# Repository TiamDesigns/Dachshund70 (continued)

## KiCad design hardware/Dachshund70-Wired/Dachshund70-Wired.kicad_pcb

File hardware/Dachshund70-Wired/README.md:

# Dachshund70 wired mainboard

Rev 1.4 (2026-11-24). A wired-only mainboard next to the tri-mode one (`hardware/Dachshund70/`, unchanged): no
radio, no battery, an RP2350B, an SK6812MINI-E under every key and hot-swap sockets on every key. KiCad 10, 2 layers,
same outline as mainboard rev 1.4 (x 19 to 326, y 39 to 160.1, the MCU column on the right), every part on the back,
so it drops into the same plate, case and flex.

Status: schematic ERC 0; board DRC clean (0 violations, 0 unconnected, schematic parity clean, kicad-cli 10.0.3).
Not ordered, not tested. No firmware yet: the RP2350 port is in `SCHEDULED_TASKS.md`.

Rev 1.0 had an RP2040 and a small SPI TFT; rev 1.1 swaps in the RP2350B so the screen can be a 2.41" AMOLED
(450 × 600, RM690B0 driver) on quad SPI, which the RP2040 couldn't drive at a useful frame rate. Rev 1.2 adds the
touch version of that screen: J4 grows to 16 pins for its touch controller's I2C, interrupt and reset. Rev 1.3
switches the screen to e-paper with capacitive touch, since the screen is mostly for changing settings; rev 1.4
picks the panel: Good Display's 2.7" GDEY027T91-FT11 (264 × 176, capacitive touch, front light), which fits the
column between the knob and the arrows (the 3.7" made the keyboard too wide, the 2.9" was too long). Both keep rev
1.2's copper and GPIOs, with the screen lines renamed.

## What's on it

- **RP2350B** (U1, QFN-80, 10 × 10 mm) with a W25Q128JVSIQ flash (U2, 16 MB), 12 MHz crystal (Y1, ABM8-272-T3,
  15 pF, 1k on XOUT), its own 1.1 V switching regulator (L1 3.3 µH, C9 4.7 µF in, C10 4.7 µF out, VREG_AVDD
  through R11 33 Ω with C27), 100 nF on the power pins, BOOT (SW1, QSPI_SS to GND through 1k) and RESET (SW2)
  buttons, and SWDIO/SWCLK test pads (TP5, TP6). The ROM has a UF2 bootloader (hold BOOT at reset), so flashing
  stays drag-and-drop.
- **77 keys**, 6.25u spacebar only (no split layout), Kailh-pattern hot-swap sockets (HanElectricity
  CPG151101S11-2, C49352235) on every key, a 1N4148W per key, COL2ROW.
- **77 SK6812MINI-E** reverse-mount LEDs (LED1-LED77), one under each key at the switch's LED window
  (key centre + 5.08 mm), through a 3.4 mm light cutout, each with a 100 nF cap. The chain is serpentine:
  LED1 is Delete, the top row runs right to left, the next left to right, and so on; LED77 is Right arrow.
- **LED power:** an AO3401A (Q1) switches VBUS to LED_5V, driven by a 2N7002 (Q2) from GPIO1 (LED_EN, 100k
  pull-down so the LEDs stay off through reset and USB suspend). R6/C19 slow its turn-on so the 77 LED caps and
  C18 (22 µF) don't pull VBUS down. A 74AHCT1G125 (U4) powered from LED_5V lifts the 3.3 V data to 5 V (33 Ω out).
- **3.3 V** from an ME6211C33 (U3, 500 mA) on VBUS.
- **Connectors**, all at the edge with their mouths out, in rev 1.4's places:
  - J1 (JST-SH 6P) to the hub board or the old USB-C board: 1 VBUS, 2 D−, 3 D+, 4 GND, 5-6 not connected.
    The old daughterboard (`hardware/Dachshund70-USB`) still fits for a Lite build; its slide switch does nothing.
  - J4 (FH12-16S FFC, LCSC C596731) to the screen: 1-2 +3V3, 3 GND, 4 TP_RST, 5 GND, 6 TP_INT, 7 TP_SCL,
    8 TP_SDA, 9 FL_PWM (front light), 10 TP_EN, 11 EPD_BUSY, 12 EPD_RST, 13 EPD_DC, 14 EPD_MOSI, 15 EPD_SCK, 16 EPD_CS.
    The e-paper's SPI is on the RP2350's SPI0 pins (CS GPIO33, SCK 34, MOSI 35) and its touch controller (I2C,
    an FT6336U) on I2C1 (GPIO42/43) with 4.7k pull-ups on the board (R12, R13). The twelve lines run as one bus
    with no crossings (J4's order is the chip's, reversed). J4 sits 1.5 mm lower than rev 1.1's 12-pin one (centre
    y 119.4). The panel comes bare on its own FPCs (e-paper, touch, front light), so a small adapter board goes between:
    see Open checks.
  - J5 (JST-SH 5P) encoder, unchanged: 1 COL14, 2 ENC_A, 3 GND, 4 ENC_B, 5 ENC_SW (push switch at row 0, col 14
    through D114).

## Pin map (RP2350B)

| GPIO | Net | | GPIO | Net |
|---|---|---|---|---|
| 0 | LED data (PIO, through U4) | | 33 | EPD_CS (SPI0 CSn) |
| 1 | LED_EN | | 34 | EPD_SCK (SPI0) |
| 2-3 | not connected | | 35 | EPD_MOSI (SPI0 TX) |
| 4-14 | COL4-COL14 | | 36 | EPD_DC |
| 15-20 | ROW0-ROW5 | | 37 | EPD_RST |
| 21-24 | COL0-COL3 | | 38 | EPD_BUSY |
| 25-26 | ENC_A, ENC_B | | 39 | TP_EN (touch power, optional) |
| 27-32 | not connected | | 40 | FL_PWM (front light dimming, on J4 pin 9) |
| | | | 42, 43 | TP_SDA, TP_SCL (I2C1) |
| | | | 44, 45 | TP_INT, TP_RST |
| | | | 41, 46, 47 | not connected (ADC pins free) |

The schematic is the reference: the left side of the chip carries the matrix (COL4-COL14, ROW0-ROW5) and the right
side the screen and touch, so neither crosses the other. Scan the matrix with pull-ups (drive rows low, read columns): the
RP2350's erratum E9 makes its internal pull-downs unreliable.

Rows and columns follow `boards/Dachshund70/README.md`'s matrix (row 5, col 6 is the 6.25u spacebar; row 5 cols 4
and 8 are gone with the split layout).

## Power budget

The board is bus-powered through the hub (or a plain USB-C board). 77 LEDs at full white would draw about 2.8 A,
far over USB's 500 mA (or 900 mA / 1.5 A on hosts that offer it), and on the hub the keyboard shares the PC's port
with the back ports. The firmware must cap the LEDs' total brightness, for example to about 300 mA at the default,
and turn LED_EN off in USB suspend. There's no battery, so the old battery-life limits no longer apply.

## Layout notes

- Two layers. The matrix runs mostly as horizontal tracks on the front and vertical ones on the back. The
  RP2350B's left (matrix) and right (screen) pins fan out in a staircase to staggered via columns. Its power pins
  join short rings inside the pad ring: +3V3 in three arcs tied together on the front under the chip, +1V1 in an
  arch over the exposed pad, and PGND straight into the exposed pad. The regulator's inductor and caps sit at the
  chip's bottom-right corner, next to VREG_LX/VREG_FB/VREG_AVDD, with their grounds on short links to vias.
- The screen and touch lines (e-paper SPI, touch I2C) leave the chip's right side and J4's pins in a staircase to via columns and run
  between them as a fixed twelve-line bus on the front, nested so no two cross. The crystal is turned so XIN and
  XOUT are short, with a ground guard under it between them.
- Ground: a pour on both layers, with one via per cut-off pour area (no via grid), placed by `tools/stitch.py`,
  plus short ground links where a pad sat in a cut-off island. Ground pads too boxed in for two thermal spokes join
  the pour solid (rule in `Dachshund70-Wired.kicad_dru`).
- Netclasses: Default 0.15 mm track and clearance (inside JLCPCB's 2-layer limits), Power (LED_5V, VBUS) 0.5 mm.
- Crowded reference texts (the column's passives, the stabilisers) are hidden; the fab layer keeps them.

## How it was made

The schematic was built with the KiCad MCP (Konnect): parts placed and checked through it, with the repetitive key,
LED and label grids written by script. Freerouting couldn't run on this PC, so the board was routed by a small grid
router in `tools/` (multi-source Dijkstra on a 0.1 mm grid, both layers, rip-up and reroute, then dead-end pruning).
For revs 1.1 and 1.2 only the MCU column was re-placed and re-routed (above the USB connector, plus J4's corner);
the keys, LEDs and the rest of the lower column kept rev 1.0's routing. `tools/rebuild_column.sh` re-does that from the schematic: placement in `tools/sync.py`
and `tools/col.json`, fixed fan-outs, power rings, the screen bus and ground links in `tools/prefan.py`, rev 1.0's routing cut out of
the column (`tools/cut.py`), routing plan `tools/plan_column.json` (the net order `tools/orders.py` found that
routes everything), then pour, one ground via per cut-off island (`tools/stitch.py`) and removal of one-sided vias.
It needs rev 1.0's board geometry as `geom_old.json` and the scratch folder in `S`.

## Open checks

- **Screen:** Good Display GDEY027T91-FT11: 2.7" e-paper, 264 × 176, 70.42 × 45.8 × 2.1 mm outline, 57.29 × 38.19 mm
  picture, FT6336U capacitive touch, 4-LED front light (in series, driven by a boost on the adapter). The adapter
  board is `hardware/Dachshund70-EPD/` (its README lists the checks before ordering).
- **L1:** the footprint is Murata's DFE201610P land pattern standing in for the Abracon AOTA-B201610S3R3-101-T
  (same 2016 size). Check the land pattern and the polarity dot against Abracon's drawing before ordering.

- USB D+/D− are routed as ordinary 0.15 mm tracks, not an impedance-controlled pair. Fine for 12 Mbit/s full speed
  over a few centimetres.
- 3D models and the case: the hub board and the screen board change the case (`SCHEDULED_TASKS.md`).

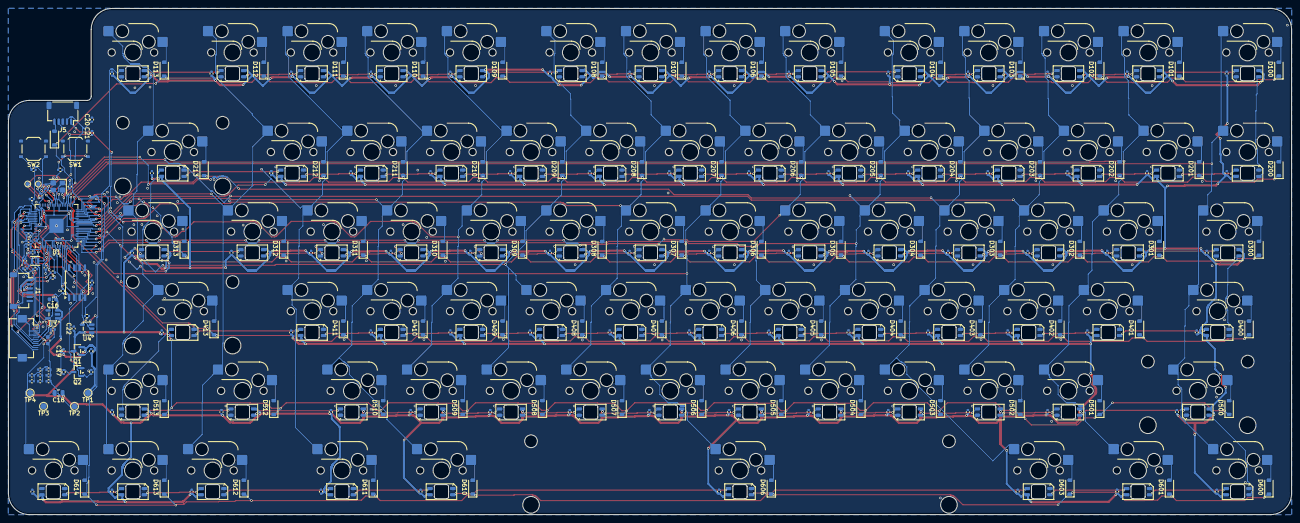
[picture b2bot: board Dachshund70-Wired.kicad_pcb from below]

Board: 2 copper layers, 307.0 x 121.1 mm, 370 parts (289 on the bottom side), 215 nets.

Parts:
C1, C2, C3, C4, C5, C6, C7, C8, C11, C12, C15, C19, C22, C24, C25, C26, C101, C102, C103, C104, C105, C106, C107, C108, C109, C110, C111, C112, C113, C114, C115, C116, C117, C118, C119, C120, C121, C122, C123, C124, C125, C126, C127, C128, C129, C130, C131, C132, C133, C134, C135, C136, C137, C138, C139, C140, C141, C142, C143, C144, C145, C146, C147, C148, C149, C150, C151, C152, C153, C154, C155, C156, C157, C158, C159, C160, C161, C162, C163, C164, C165, C166, C167, C168, C169, C170, C171, C172, C173, C174, C175, C176, C177: 100nF; C_0402_1005Metric
C9, C10, C27: 4.7uF; C_0402_1005Metric
C13, C14: 15pF; C_0402_1005Metric
C16, C23: 10uF; C_0603_1608Metric
C17: 10uF; C_0402_1005Metric
C18: 22uF; C_0805_2012Metric
C20, C21: 10nF; C_0402_1005Metric
D100, D101, D102, D103, D104, D105, D106, D107, D108, D109, D110, D111, D112, D113, D114, D200, D201, D202, D203, D204, D205, D206, D207, D208, D209, D210, D211, D212, D213, D300, D301, D302, D303, D304, D305, D306, D307, D308, D309, D310, D311, D312, D313, D400, D401, D402, D403, D404, D405, D406, D407, D408, D409, D410, D411, D413, D500, D501, D502, D503, D504, D505, D506, D507, D508, D509, D510, D512, D513, D600, D601, D603, D606, D610, D611, D612, D613, D614: 1N4148W; D_SOD-123
J1: USB in (JST-SH 6P); JST_SH_SM06B-SRSS-TB_1x06-1MP_P1.00mm_Horizontal
J4: Display (FFC 12P 0.5 mm, QSPI); Hirose_FH12-12S-0.5SH_1x12-1MP_P0.50mm_Horizontal
J5: Encoder (JST-SH 5P); JST_SH_SM05B-SRSS-TB_1x05-1MP_P1.00mm_Horizontal
L1: 3.3uH; L_Murata_DFE201610P
LED1: SK6812MINI-E (Delete); LED_SK6812MINI-E_3.2x2.8mm_P1.5mm_ReverseMount_Cutout3.4
LED2: SK6812MINI-E (F12); LED_SK6812MINI-E_3.2x2.8mm_P1.5mm_ReverseMount_Cutout3.4
LED3: SK6812MINI-E (F11); LED_SK6812MINI-E_3.2x2.8mm_P1.5mm_ReverseMount_Cutout3.4
LED4: SK6812MINI-E (F10); LED_SK6812MINI-E_3.2x2.8mm_P1.5mm_ReverseMount_Cutout3.4
LED5: SK6812MINI-E (F9); LED_SK6812MINI-E_3.2x2.8mm_P1.5mm_ReverseMount_Cutout3.4
LED6: SK6812MINI-E (F8); LED_SK6812MINI-E_3.2x2.8mm_P1.5mm_ReverseMount_Cutout3.4
LED7: SK6812MINI-E (F7); LED_SK6812MINI-E_3.2x2.8mm_P1.5mm_ReverseMount_Cutout3.4
LED8: SK6812MINI-E (F6); LED_SK6812MINI-E_3.2x2.8mm_P1.5mm_ReverseMount_Cutout3.4
LED9: SK6812MINI-E (F5); LED_SK6812MINI-E_3.2x2.8mm_P1.5mm_ReverseMount_Cutout3.4
LED10: SK6812MINI-E (F4); LED_SK6812MINI-E_3.2x2.8mm_P1.5mm_ReverseMount_Cutout3.4
LED11: SK6812MINI-E (F3); LED_SK6812MINI-E_3.2x2.8mm_P1.5mm_ReverseMount_Cutout3.4
LED12: SK6812MINI-E (F2); LED_SK6812MINI-E_3.2x2.8mm_P1.5mm_ReverseMount_Cutout3.4
LED13: SK6812MINI-E (F1); LED_SK6812MINI-E_3.2x2.8mm_P1.5mm_ReverseMount_Cutout3.4
LED14: SK6812MINI-E (Esc); LED_SK6812MINI-E_3.2x2.8mm_P1.5mm_ReverseMount_Cutout3.4
LED15: SK6812MINI-E (`); LED_SK6812MINI-E_3.2x2.8mm_P1.5mm_ReverseMount_Cutout3.4
LED16: SK6812MINI-E (1); LED_SK6812MINI-E_3.2x2.8mm_P1.5mm_ReverseMount_Cutout3.4
LED17: SK6812MINI-E (2); LED_SK6812MINI-E_3.2x2.8mm_P1.5mm_ReverseMount_Cutout3.4
LED18: SK6812MINI-E (3); LED_SK6812MINI-E_3.2x2.8mm_P1.5mm_ReverseMount_Cutout3.4
LED19: SK6812MINI-E (4); LED_SK6812MINI-E_3.2x2.8mm_P1.5mm_ReverseMount_Cutout3.4
LED20: SK6812MINI-E (5); LED_SK6812MINI-E_3.2x2.8mm_P1.5mm_ReverseMount_Cutout3.4
LED21: SK6812MINI-E (6); LED_SK6812MINI-E_3.2x2.8mm_P1.5mm_ReverseMount_Cutout3.4
LED22: SK6812MINI-E (7); LED_SK6812MINI-E_3.2x2.8mm_P1.5mm_ReverseMount_Cutout3.4
LED23: SK6812MINI-E (8); LED_SK6812MINI-E_3.2x2.8mm_P1.5mm_ReverseMount_Cutout3.4
LED24: SK6812MINI-E (9); LED_SK6812MINI-E_3.2x2.8mm_P1.5mm_ReverseMount_Cutout3.4
LED25: SK6812MINI-E (0); LED_SK6812MINI-E_3.2x2.8mm_P1.5mm_ReverseMount_Cutout3.4
LED26: SK6812MINI-E (-); LED_SK6812MINI-E_3.2x2.8mm_P1.5mm_ReverseMount_Cutout3.4
LED27: SK6812MINI-E (=); LED_SK6812MINI-E_3.2x2.8mm_P1.5mm_ReverseMount_Cutout3.4
LED28: SK6812MINI-E (Backspace); LED_SK6812MINI-E_3.2x2.8mm_P1.5mm_ReverseMount_Cutout3.4
LED29: SK6812MINI-E (Backslash); LED_SK6812MINI-E_3.2x2.8mm_P1.5mm_ReverseMount_Cutout3.4
LED30: SK6812MINI-E (]); LED_SK6812MINI-E_3.2x2.8mm_P1.5mm_ReverseMount_Cutout3.4
LED31: SK6812MINI-E ([); LED_SK6812MINI-E_3.2x2.8mm_P1.5mm_ReverseMount_Cutout3.4
LED32: SK6812MINI-E (P); LED_SK6812MINI-E_3.2x2.8mm_P1.5mm_ReverseMount_Cutout3.4
LED33: SK6812MINI-E (O); LED_SK6812MINI-E_3.2x2.8mm_P1.5mm_ReverseMount_Cutout3.4
LED34: SK6812MINI-E (I); LED_SK6812MINI-E_3.2x2.8mm_P1.5mm_ReverseMount_Cutout3.4
LED35: SK6812MINI-E (U); LED_SK6812MINI-E_3.2x2.8mm_P1.5mm_ReverseMount_Cutout3.4
LED36: SK6812MINI-E (Y); LED_SK6812MINI-E_3.2x2.8mm_P1.5mm_ReverseMount_Cutout3.4
LED37: SK6812MINI-E (T); LED_SK6812MINI-E_3.2x2.8mm_P1.5mm_ReverseMount_Cutout3.4
LED38: SK6812MINI-E (R); LED_SK6812MINI-E_3.2x2.8mm_P1.5mm_ReverseMount_Cutout3.4
LED39: SK6812MINI-E (E); LED_SK6812MINI-E_3.2x2.8mm_P1.5mm_ReverseMount_Cutout3.4
LED40: SK6812MINI-E (W); LED_SK6812MINI-E_3.2x2.8mm_P1.5mm_ReverseMount_Cutout3.4
LED41: SK6812MINI-E (Q); LED_SK6812MINI-E_3.2x2.8mm_P1.5mm_ReverseMount_Cutout3.4
LED42: SK6812MINI-E (Tab); LED_SK6812MINI-E_3.2x2.8mm_P1.5mm_ReverseMount_Cutout3.4
LED43: SK6812MINI-E (Caps Lock); LED_SK6812MINI-E_3.2x2.8mm_P1.5mm_ReverseMount_Cutout3.4
LED44: SK6812MINI-E (A); LED_SK6812MINI-E_3.2x2.8mm_P1.5mm_ReverseMount_Cutout3.4
LED45: SK6812MINI-E (S); LED_SK6812MINI-E_3.2x2.8mm_P1.5mm_ReverseMount_Cutout3.4
LED46: SK6812MINI-E (D); LED_SK6812MINI-E_3.2x2.8mm_P1.5mm_ReverseMount_Cutout3.4
LED47: SK6812MINI-E (F); LED_SK6812MINI-E_3.2x2.8mm_P1.5mm_ReverseMount_Cutout3.4
LED48: SK6812MINI-E (G); LED_SK6812MINI-E_3.2x2.8mm_P1.5mm_ReverseMount_Cutout3.4
LED49: SK6812MINI-E (H); LED_SK6812MINI-E_3.2x2.8mm_P1.5mm_ReverseMount_Cutout3.4
LED50: SK6812MINI-E (J); LED_SK6812MINI-E_3.2x2.8mm_P1.5mm_ReverseMount_Cutout3.4
LED51: SK6812MINI-E (K); LED_SK6812MINI-E_3.2x2.8mm_P1.5mm_ReverseMount_Cutout3.4
LED52: SK6812MINI-E (L); LED_SK6812MINI-E_3.2x2.8mm_P1.5mm_ReverseMount_Cutout3.4
LED53: SK6812MINI-E (;); LED_SK6812MINI-E_3.2x2.8mm_P1.5mm_ReverseMount_Cutout3.4
LED54: SK6812MINI-E ('); LED_SK6812MINI-E_3.2x2.8mm_P1.5mm_ReverseMount_Cutout3.4
LED55: SK6812MINI-E (Enter); LED_SK6812MINI-E_3.2x2.8mm_P1.5mm_ReverseMount_Cutout3.4
LED56: SK6812MINI-E (Up); LED_SK6812MINI-E_3.2x2.8mm_P1.5mm_ReverseMount_Cutout3.4
LED57, LED68: SK6812MINI-E (Shift); LED_SK6812MINI-E_3.2x2.8mm_P1.5mm_ReverseMount_Cutout3.4
LED58: SK6812MINI-E (/); LED_SK6812MINI-E_3.2x2.8mm_P1.5mm_ReverseMount_Cutout3.4
LED59: SK6812MINI-E (.); LED_SK6812MINI-E_3.2x2.8mm_P1.5mm_ReverseMount_Cutout3.4
LED60: SK6812MINI-E (,); LED_SK6812MINI-E_3.2x2.8mm_P1.5mm_ReverseMount_Cutout3.4
LED61: SK6812MINI-E (M); LED_SK6812MINI-E_3.2x2.8mm_P1.5mm_ReverseMount_Cutout3.4
LED62: SK6812MINI-E (N); LED_SK6812MINI-E_3.2x2.8mm_P1.5mm_ReverseMount_Cutout3.4
LED63: SK6812MINI-E (B); LED_SK6812MINI-E_3.2x2.8mm_P1.5mm_ReverseMount_Cutout3.4
LED64: SK6812MINI-E (V); LED_SK6812MINI-E_3.2x2.8mm_P1.5mm_ReverseMount_Cutout3.4
LED65: SK6812MINI-E (C); LED_SK6812MINI-E_3.2x2.8mm_P1.5mm_ReverseMount_Cutout3.4
LED66: SK6812MINI-E (X); LED_SK6812MINI-E_3.2x2.8mm_P1.5mm_ReverseMount_Cutout3.4
LED67: SK6812MINI-E (Z); LED_SK6812MINI-E_3.2x2.8mm_P1.5mm_ReverseMount_Cutout3.4
LED69, LED74: SK6812MINI-E (Ctrl); LED_SK6812MINI-E_3.2x2.8mm_P1.5mm_ReverseMount_Cutout3.4
LED70: SK6812MINI-E (Win); LED_SK6812MINI-E_3.2x2.8mm_P1.5mm_ReverseMount_Cutout3.4
LED71: SK6812MINI-E (Alt); LED_SK6812MINI-E_3.2x2.8mm_P1.5mm_ReverseMount_Cutout3.4
LED72: SK6812MINI-E (Space); LED_SK6812MINI-E_3.2x2.8mm_P1.5mm_ReverseMount_Cutout3.4
LED73: SK6812MINI-E (Fn); LED_SK6812MINI-E_3.2x2.8mm_P1.5mm_ReverseMount_Cutout3.4
LED75: SK6812MINI-E (Left); LED_SK6812MINI-E_3.2x2.8mm_P1.5mm_ReverseMount_Cutout3.4
LED76: SK6812MINI-E (Down); LED_SK6812MINI-E_3.2x2.8mm_P1.5mm_ReverseMount_Cutout3.4
LED77: SK6812MINI-E (Right); LED_SK6812MINI-E_3.2x2.8mm_P1.5mm_ReverseMount_Cutout3.4
Q1: AO3401A; SOT-23
Q2: 2N7002; SOT-23
R1, R2: 27; R_0402_1005Metric
R3, R4: 1k; R_0402_1005Metric
R5, R7, R10: 10k; R_0402_1005Metric
R6, R8: 100k; R_0402_1005Metric
R9, R11: 33; R_0402_1005Metric
ST1: Stab Backspace 2.00u; Stabilizer_Cherry_MX_2.00u
ST2: Stab Enter 2.25u; Stabilizer_Cherry_MX_2.00u
ST3: Stab Shift 2.25u; Stabilizer_Cherry_MX_2.00u
ST4: Stab Space 6.25u; Stabilizer_Cherry_MX_6.25u
SW1: BOOT; SW_Push_1P1T_XKB_TS-1187A
SW2: RESET; SW_Push_1P1T_XKB_TS-1187A
SW100: MX Esc (1.00u); SW_Hotswap_Kailh_MX_1.00u
SW101: MX F1 (1.00u); SW_Hotswap_Kailh_MX_1.00u
SW102: MX F2 (1.00u); SW_Hotswap_Kailh_MX_1.00u
SW103: MX F3 (1.00u); SW_Hotswap_Kailh_MX_1.00u
SW104: MX F4 (1.00u); SW_Hotswap_Kailh_MX_1.00u
SW105: MX F5 (1.00u); SW_Hotswap_Kailh_MX_1.00u
SW106: MX F6 (1.00u); SW_Hotswap_Kailh_MX_1.00u
SW107: MX F7 (1.00u); SW_Hotswap_Kailh_MX_1.00u
SW108: MX F8 (1.00u); SW_Hotswap_Kailh_MX_1.00u
SW109: MX F9 (1.00u); SW_Hotswap_Kailh_MX_1.00u
SW110: MX F10 (1.00u); SW_Hotswap_Kailh_MX_1.00u
SW111: MX F11 (1.00u); SW_Hotswap_Kailh_MX_1.00u
SW112: MX F12 (1.00u); SW_Hotswap_Kailh_MX_1.00u
SW113: MX Delete (1.00u); SW_Hotswap_Kailh_MX_1.00u
SW200: MX ` (1.00u); SW_Hotswap_Kailh_MX_1.00u
SW201: MX 1 (1.00u); SW_Hotswap_Kailh_MX_1.00u
SW202: MX 2 (1.00u); SW_Hotswap_Kailh_MX_1.00u
SW203: MX 3 (1.00u); SW_Hotswap_Kailh_MX_1.00u
SW204: MX 4 (1.00u); SW_Hotswap_Kailh_MX_1.00u
SW205: MX 5 (1.00u); SW_Hotswap_Kailh_MX_1.00u
SW206: MX 6 (1.00u); SW_Hotswap_Kailh_MX_1.00u
SW207: MX 7 (1.00u); SW_Hotswap_Kailh_MX_1.00u
SW208: MX 8 (1.00u); SW_Hotswap_Kailh_MX_1.00u
SW209: MX 9 (1.00u); SW_Hotswap_Kailh_MX_1.00u
SW210: MX 0 (1.00u); SW_Hotswap_Kailh_MX_1.00u
SW211: MX - (1.00u); SW_Hotswap_Kailh_MX_1.00u
SW212: MX = (1.00u); SW_Hotswap_Kailh_MX_1.00u
SW213: MX Backspace (2.00u); SW_Hotswap_Kailh_MX_2.00u
SW300: MX Tab (1.50u); SW_Hotswap_Kailh_MX_1.50u
SW301: MX Q (1.00u); SW_Hotswap_Kailh_MX_1.00u
SW302: MX W (1.00u); SW_Hotswap_Kailh_MX_1.00u
SW303: MX E (1.00u); SW_Hotswap_Kailh_MX_1.00u
SW304: MX R (1.00u); SW_Hotswap_Kailh_MX_1.00u
SW305: MX T (1.00u); SW_Hotswap_Kailh_MX_1.00u
SW306: MX Y (1.00u); SW_Hotswap_Kailh_MX_1.00u
SW307: MX U (1.00u); SW_Hotswap_Kailh_MX_1.00u
SW308: MX I (1.00u); SW_Hotswap_Kailh_MX_1.00u
SW309: MX O (1.00u); SW_Hotswap_Kailh_MX_1.00u
SW310: MX P (1.00u); SW_Hotswap_Kailh_MX_1.00u
SW311: MX [ (1.00u); SW_Hotswap_Kailh_MX_1.00u
SW312: MX ] (1.00u); SW_Hotswap_Kailh_MX_1.00u
SW313: MX Backslash (1.50u); SW_Hotswap_Kailh_MX_1.50u
SW400: MX Caps Lock (1.75u); SW_Hotswap_Kailh_MX_1.75u
SW401: MX A (1.00u); SW_Hotswap_Kailh_MX_1.00u
SW402: MX S (1.00u); SW_Hotswap_Kailh_MX_1.00u
SW403: MX D (1.00u); SW_Hotswap_Kailh_MX_1.00u
SW404: MX F (1.00u); SW_Hotswap_Kailh_MX_1.00u
SW405: MX G (1.00u); SW_Hotswap_Kailh_MX_1.00u
SW406: MX H (1.00u); SW_Hotswap_Kailh_MX_1.00u
SW407: MX J (1.00u); SW_Hotswap_Kailh_MX_1.00u
SW408: MX K (1.00u); SW_Hotswap_Kailh_MX_1.00u
SW409: MX L (1.00u); SW_Hotswap_Kailh_MX_1.00u
SW410: MX ; (1.00u); SW_Hotswap_Kailh_MX_1.00u
SW411: MX ' (1.00u); SW_Hotswap_Kailh_MX_1.00u
SW413: MX Enter (2.25u); SW_Hotswap_Kailh_MX_2.25u
SW500: MX Shift (2.25u); SW_Hotswap_Kailh_MX_2.25u
SW501: MX Z (1.00u); SW_Hotswap_Kailh_MX_1.00u
SW502: MX X (1.00u); SW_Hotswap_Kailh_MX_1.00u
SW503: MX C (1.00u); SW_Hotswap_Kailh_MX_1.00u
SW504: MX V (1.00u); SW_Hotswap_Kailh_MX_1.00u
SW505: MX B (1.00u); SW_Hotswap_Kailh_MX_1.00u
SW506: MX N (1.00u); SW_Hotswap_Kailh_MX_1.00u
SW507: MX M (1.00u); SW_Hotswap_Kailh_MX_1.00u
SW508: MX , (1.00u); SW_Hotswap_Kailh_MX_1.00u
SW509: MX . (1.00u); SW_Hotswap_Kailh_MX_1.00u
SW510: MX / (1.00u); SW_Hotswap_Kailh_MX_1.00u
SW512: MX Shift (1.75u); SW_Hotswap_Kailh_MX_1.75u
SW513: MX Up (1.00u); SW_Hotswap_Kailh_MX_1.00u
SW600, SW611: MX Ctrl (1.25u); SW_Hotswap_Kailh_MX_1.25u
SW601: MX Win (1.25u); SW_Hotswap_Kailh_MX_1.25u
SW603: MX Alt (1.25u); SW_Hotswap_Kailh_MX_1.25u
SW606: MX Space (6.25u); SW_Hotswap_Kailh_MX_6.25u
SW610: MX Fn (1.25u); SW_Hotswap_Kailh_MX_1.25u
SW612: MX Left (1.00u); SW_Hotswap_Kailh_MX_1.00u
SW613: MX Down (1.00u); SW_Hotswap_Kailh_MX_1.00u
SW614: MX Right (1.00u); SW_Hotswap_Kailh_MX_1.00u
TP1: VBUS; TestPoint_Pad_D1.5mm
TP2: +3V3; TestPoint_Pad_D1.5mm
TP3: GND; TestPoint_Pad_D1.5mm
TP4: LED_5V; TestPoint_Pad_D1.5mm
TP5: SWDIO; TestPoint_Pad_D1.0mm
TP6: SWCLK; TestPoint_Pad_D1.0mm
U1: RP2350B; QFN-80-1EP_10x10mm_P0.4mm_EP3.4x3.4mm
U2: W25Q128JVSIQ; SOIC-8_5.3x5.3mm_P1.27mm
U3: ME6211C33M5G-N; SOT-23-5
U4: 74AHCT1G125; SOT-23-5
Y1: ABM8-272-T3; Crystal_SMD_3225-4Pin_3.2x2.5mm

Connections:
+1V1: C7.1, C8.1, C10.1, L1.2, U1.10, U1.32, U1.51, U1.65
+3V3: C1.1, C2.1, C3.1, C4.1, C5.1, C6.1, C9.1, C11.1, C12.1, C15.1, C17.1, C23.1, C24.1, C25.1, C26.1, J4.1, J4.2, R5.1, R10.1, R11.1, TP2.1, U1.5, U1.15, U1.24, U1.29, U1.41, U1.50, U1.59, U1.60, U1.64, U1.68, U1.69, U1.76, U2.8, U3.5
/BOOT_SW: R4.2, SW1.1
/COL0: SW100.2, SW200.2, SW300.2, SW400.2, SW500.2, SW600.2, U1.21
/COL1: SW101.2, SW201.2, SW301.2, SW401.2, SW501.2, SW601.2, U1.22
/COL2: SW102.2, SW202.2, SW302.2, SW402.2, SW502.2, U1.23
/COL3: SW103.2, SW203.2, SW303.2, SW403.2, SW503.2, SW603.2, U1.25
/COL4: SW104.2, SW204.2, SW304.2, SW404.2, SW504.2, U1.1
/COL5: SW105.2, SW205.2, SW305.2, SW405.2, SW505.2, U1.2
/COL6: SW106.2, SW206.2, SW306.2, SW406.2, SW506.2, SW606.2, U1.3
/COL7: SW107.2, SW207.2, SW307.2, SW407.2, SW507.2, U1.4
/COL8: SW108.2, SW208.2, SW308.2, SW408.2, SW508.2, U1.6
/COL9: SW109.2, SW209.2, SW309.2, SW409.2, SW509.2, U1.7
/COL10: SW110.2, SW210.2, SW310.2, SW410.2, SW510.2, SW610.2, U1.8
/COL11: SW111.2, SW211.2, SW311.2, SW411.2, SW611.2, U1.9
/COL12: SW112.2, SW212.2, SW312.2, SW512.2, SW612.2, U1.11
/COL13: SW113.2, SW213.2, SW313.2, SW413.2, SW513.2, SW613.2, U1.12
/COL14: J5.1, SW614.2, U1.13
/DISP_CLK: J4.4, U1.46
/DISP_CS: J4.10, U1.47
/DISP_D0: J4.6, U1.42
/DISP_D1: J4.7, U1.43
/DISP_D2: J4.8, U1.44
/DISP_D3: J4.9, U1.45
/DISP_RST: J4.11, U1.48
/DISP_TE: J4.12, U1.49
/ENC_A: C20.1, J5.2, U1.26
/ENC_B: C21.1, J5.4, U1.27
/ENC_SW: D114.2, J5.5
/LED_DATA_3V3: U1.77, U4.2
/LED_DATA_5V: R9.1, U4.4
/LED_DIN: LED1.2, R9.2
/LED_EN: Q2.1, R8.1, U1.78
/Q1_G: C19.2, Q1.1, R6.2, R7.1
/Q2_D: Q2.3, R7.2
/QSPI_SCLK: U1.71, U2.6
/QSPI_SD0: U1.72, U2.5
/QSPI_SD1: U1.74, U2.2
/QSPI_SD2: U1.73, U2.3
/QSPI_SD3: U1.70, U2.7
/QSPI_SS: R4.1, R10.2, U1.75, U2.1
/ROW0: D100.1, D101.1, D102.1, D103.1, D104.1, D105.1, D106.1, D107.1, D108.1, D109.1, D110.1, D111.1, D112.1, D113.1, D114.1, U1.14
/ROW1: D200.1, D201.1, D202.1, D203.1, D204.1, D205.1, D206.1, D207.1, D208.1, D209.1, D210.1, D211.1, D212.1, D213.1, U1.16
/ROW2: D300.1, D301.1, D302.1, D303.1, D304.1, D305.1, D306.1, D307.1, D308.1, D309.1, D310.1, D311.1, D312.1, D313.1, U1.17
/ROW3: D400.1, D401.1, D402.1, D403.1, D404.1, D405.1, D406.1, D407.1, D408.1, D409.1, D410.1, D411.1, D413.1, U1.18
/ROW4: D500.1, D501.1, D502.1, D503.1, D504.1, D505.1, D506.1, D507.1, D508.1, D509.1, D510.1, D512.1, D513.1, U1.19
/ROW5: D600.1, D601.1, D603.1, D606.1, D610.1, D611.1, D612.1, D613.1, D614.1, U1.20
/RUN: R5.2, SW2.1, U1.35
/SWCLK: TP6.1, U1.33
/SWDIO: TP5.1, U1.34
/USB_DM: J1.2, R2.2
/USB_DM_MCU: R2.1, U1.66
/USB_DP: J1.3, R1.2
/USB_DP_MCU: R1.1, U1.67
/VREG_AVDD: C27.1, R11.2, U1.61
/VREG_LX: L1.1, U1.63
/XIN: C13.1, U1.30, Y1.1
/XOUT: C14.1, R3.2, Y1.3
/XOUT_R: R3.1, U1.31
GND: C1.2, C2.2, C3.2, C4.2, C5.2, C6.2, C7.2, C8.2, C9.2, C10.2, C11.2, C12.2, C13.2, C14.2, C15.2, C16.2, C17.2, C18.2, C20.2, C21.2, C22.2, C23.2, C24.2, C25.2, C26.2, C27.2, C101.2, C102.2, C103.2, C104.2, C105.2, C106.2, C107.2, C108.2, C109.2, C110.2, C111.2, C112.2, C113.2, C114.2, C115.2, C116.2, C117.2, C118.2, C119.2, C120.2, C121.2, C122.2, C123.2, C124.2, C125.2, C126.2, C127.2, C128.2, C129.2, C130.2, C131.2, C132.2, C133.2, C134.2, C135.2, C136.2, C137.2, C138.2, C139.2, C140.2, C141.2, C142.2, C143.2, C144.2, C145.2, C146.2, C147.2, C148.2, C149.2, C150.2, C151.2, C152.2, C153.2, C154.2, C155.2, C156.2, C157.2, C158.2, C159.2, C160.2, C161.2, C162.2, C163.2, C164.2, C165.2, C166.2, C167.2, C168.2, C169.2, C170.2, C171.2, C172.2, C173.2, C174.2, C175.2, C176.2, C177.2, J1.4, J1.MP, J4.3, J4.5, J4.MP, J5.3, J5.MP, LED1.1, LED2.1, LED3.1, LED4.1, LED5.1, LED6.1, LED7.1, LED8.1, LED9.1, LED10.1, LED11.1, LED12.1, LED13.1, LED14.1, LED15.1, LED16.1, LED17.1, LED18.1, LED19.1, LED20.1, LED21.1, LED22.1, LED23.1, LED24.1, LED25.1, LED26.1, LED27.1, LED28.1, LED29.1, LED30.1, LED31.1, LED32.1, LED33.1, LED34.1, LED35.1, LED36.1, LED37.1, LED38.1, LED39.1, LED40.1, LED41.1, LED42.1, LED43.1, LED44.1, LED45.1, LED46.1, LED47.1, LED48.1, LED49.1, LED50.1, LED51.1, LED52.1, LED53.1, LED54.1, LED55.1, LED56.1, LED57.1, LED58.1, LED59.1, LED60.1, LED61.1, LED62.1, LED63.1, LED64.1, LED65.1, LED66.1, LED67.1, LED68.1, LED69.1, LED70.1, LED71.1, LED72.1, LED73.1, LED74.1, LED75.1, LED76.1, LED77.1, Q2.2, R8.2, SW1.2, SW2.2, TP3.1, U1.62, U1.81, U2.4, U3.2, U4.1, U4.3, Y1.2, Y1.4
LED_5V: C18.1, C22.1, C101.1, C102.1, C103.1, C104.1, C105.1, C106.1, C107.1, C108.1, C109.1, C110.1, C111.1, C112.1, C113.1, C114.1, C115.1, C116.1, C117.1, C118.1, C119.1, C120.1, C121.1, C122.1, C123.1, C124.1, C125.1, C126.1, C127.1, C128.1, C129.1, C130.1, C131.1, C132.1, C133.1, C134.1, C135.1, C136.1, C137.1, C138.1, C139.1, C140.1, C141.1, C142.1, C143.1, C144.1, C145.1, C146.1, C147.1, C148.1, C149.1, C150.1, C151.1, C152.1, C153.1, C154.1, C155.1, C156.1, C157.1, C158.1, C159.1, C160.1, C161.1, C162.1, C163.1, C164.1, C165.1, C166.1, C167.1, C168.1, C169.1, C170.1, C171.1, C172.1, C173.1, C174.1, C175.1, C176.1, C177.1, LED1.3, LED2.3, LED3.3, LED4.3, LED5.3, LED6.3, LED7.3, LED8.3, LED9.3, LED10.3, LED11.3, LED12.3, LED13.3, LED14.3, LED15.3, LED16.3, LED17.3, LED18.3, LED19.3, LED20.3, LED21.3, LED22.3, LED23.3, LED24.3, LED25.3, LED26.3, LED27.3, LED28.3, LED29.3, LED30.3, LED31.3, LED32.3, LED33.3, LED34.3, LED35.3, LED36.3, LED37.3, LED38.3, LED39.3, LED40.3, LED41.3, LED42.3, LED43.3, LED44.3, LED45.3, LED46.3, LED47.3, LED48.3, LED49.3, LED50.3, LED51.3, LED52.3, LED53.3, LED54.3, LED55.3, LED56.3, LED57.3, LED58.3, LED59.3, LED60.3, LED61.3, LED62.3, LED63.3, LED64.3, LED65.3, LED66.3, LED67.3, LED68.3, LED69.3, LED70.3, LED71.3, LED72.3, LED73.3, LED74.3, LED75.3, LED76.3, LED77.3, Q1.3, TP4.1, U4.5
unnamed: D100.2, SW100.1
unnamed: D101.2, SW101.1
unnamed: D102.2, SW102.1
unnamed: D103.2, SW103.1
unnamed: D104.2, SW104.1
unnamed: D105.2, SW105.1
unnamed: D106.2, SW106.1
unnamed: D107.2, SW107.1
unnamed: D108.2, SW108.1
unnamed: D109.2, SW109.1
unnamed: D110.2, SW110.1
unnamed: D111.2, SW111.1
unnamed: D112.2, SW112.1
unnamed: D113.2, SW113.1
unnamed: D200.2, SW200.1
unnamed: D201.2, SW201.1
unnamed: D202.2, SW202.1
unnamed: D203.2, SW203.1
unnamed: D204.2, SW204.1
unnamed: D205.2, SW205.1
unnamed: D206.2, SW206.1
unnamed: D207.2, SW207.1
unnamed: D208.2, SW208.1
unnamed: D209.2, SW209.1
unnamed: D210.2, SW210.1
unnamed: D211.2, SW211.1
unnamed: D212.2, SW212.1
unnamed: D213.2, SW213.1
unnamed: D300.2, SW300.1
unnamed: D301.2, SW301.1
unnamed: D302.2, SW302.1
unnamed: D303.2, SW303.1
unnamed: D304.2, SW304.1
unnamed: D305.2, SW305.1
unnamed: D306.2, SW306.1
unnamed: D307.2, SW307.1
unnamed: D308.2, SW308.1
unnamed: D309.2, SW309.1
unnamed: D310.2, SW310.1
unnamed: D311.2, SW311.1
unnamed: D312.2, SW312.1
unnamed: D313.2, SW313.1
unnamed: D400.2, SW400.1
unnamed: D401.2, SW401.1
unnamed: D402.2, SW402.1
unnamed: D403.2, SW403.1
unnamed: D404.2, SW404.1
unnamed: D405.2, SW405.1
unnamed: D406.2, SW406.1
unnamed: D407.2, SW407.1
unnamed: D408.2, SW408.1
unnamed: D409.2, SW409.1
unnamed: D410.2, SW410.1
unnamed: D411.2, SW411.1
unnamed: D413.2, SW413.1
unnamed: D500.2, SW500.1
unnamed: D501.2, SW501.1
unnamed: D502.2, SW502.1
unnamed: D503.2, SW503.1
unnamed: D504.2, SW504.1
unnamed: D505.2, SW505.1
unnamed: D506.2, SW506.1
unnamed: D507.2, SW507.1
unnamed: D508.2, SW508.1
unnamed: D509.2, SW509.1
unnamed: D510.2, SW510.1
unnamed: D512.2, SW512.1
unnamed: D513.2, SW513.1
unnamed: D600.2, SW600.1
unnamed: D601.2, SW601.1
unnamed: D603.2, SW603.1
unnamed: D606.2, SW606.1
unnamed: D610.2, SW610.1
unnamed: D611.2, SW611.1
unnamed: D612.2, SW612.1
unnamed: D613.2, SW613.1
unnamed: D614.2, SW614.1
unnamed: LED1.4, LED2.2
unnamed: LED2.4, LED3.2
unnamed: LED3.4, LED4.2
unnamed: LED4.4, LED5.2
unnamed: LED5.4, LED6.2
unnamed: LED6.4, LED7.2
unnamed: LED7.4, LED8.2
unnamed: LED8.4, LED9.2
unnamed: LED9.4, LED10.2
unnamed: LED10.4, LED11.2
unnamed: LED11.4, LED12.2
unnamed: LED12.4, LED13.2
unnamed: LED13.4, LED14.2
unnamed: LED14.4, LED15.2
unnamed: LED15.4, LED16.2
unnamed: LED16.4, LED17.2
unnamed: LED17.4, LED18.2
unnamed: LED18.4, LED19.2
unnamed: LED19.4, LED20.2
unnamed: LED20.4, LED21.2
unnamed: LED21.4, LED22.2
unnamed: LED22.4, LED23.2
unnamed: LED23.4, LED24.2
unnamed: LED24.4, LED25.2
unnamed: LED25.4, LED26.2
unnamed: LED26.4, LED27.2
unnamed: LED27.4, LED28.2
unnamed: LED28.4, LED29.2
unnamed: LED29.4, LED30.2
unnamed: LED30.4, LED31.2
unnamed: LED31.4, LED32.2
unnamed: LED32.4, LED33.2
unnamed: LED33.4, LED34.2
unnamed: LED34.4, LED35.2
unnamed: LED35.4, LED36.2
unnamed: LED36.4, LED37.2
unnamed: LED37.4, LED38.2
unnamed: LED38.4, LED39.2
unnamed: LED39.4, LED40.2
unnamed: LED40.4, LED41.2
unnamed: LED41.4, LED42.2
unnamed: LED42.4, LED43.2
unnamed: LED43.4, LED44.2
unnamed: LED44.4, LED45.2
unnamed: LED45.4, LED46.2
unnamed: LED46.4, LED47.2
unnamed: LED47.4, LED48.2
unnamed: LED48.4, LED49.2
unnamed: LED49.4, LED50.2
unnamed: LED50.4, LED51.2
unnamed: LED51.4, LED52.2
unnamed: LED52.4, LED53.2
unnamed: LED53.4, LED54.2
unnamed: LED54.4, LED55.2
unnamed: LED55.4, LED56.2
unnamed: LED56.4, LED57.2
unnamed: LED57.4, LED58.2
unnamed: LED58.4, LED59.2
unnamed: LED59.4, LED60.2
unnamed: LED60.4, LED61.2
unnamed: LED61.4, LED62.2
unnamed: LED62.4, LED63.2
unnamed: LED63.4, LED64.2
unnamed: LED64.4, LED65.2
unnamed: LED65.4, LED66.2
unnamed: LED66.4, LED67.2
unnamed: LED67.4, LED68.2
unnamed: LED68.4, LED69.2
unnamed: LED69.4, LED70.2
unnamed: LED70.4, LED71.2
unnamed: LED71.4, LED72.2
unnamed: LED72.4, LED73.2
unnamed: LED73.4, LED74.2
unnamed: LED74.4, LED75.2
unnamed: LED75.4, LED76.2
unnamed: LED76.4, LED77.2
VBUS: C16.1, C19.1, J1.1, Q1.2, R6.1, TP1.1, U3.1, U3.3

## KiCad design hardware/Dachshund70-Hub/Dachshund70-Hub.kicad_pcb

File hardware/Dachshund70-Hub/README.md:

# Dachshund70 USB hub board

Rev 1.0 (2026-11-24). Goes on the back of the case in place of the USB-C daughterboard, for the wired mainboard
(`hardware/Dachshund70-Wired/`). KiCad 10, 2 layers, 80 × 22 mm, every part on top, every port's mouth on the back
edge (y = 0). ERC 0; DRC clean (0 violations, 0 unconnected, schematic parity clean). Not ordered, not tested.

## Ports

| Ref | Port | Hub port | |
|---|---|---|---|
| J1 | USB-C, to the PC | upstream | CC1/CC2 5.1k pull-downs, USBLC6 (U2), 1.1 A PTC (F1) |
| J2 | JST-SH 6P, to the keyboard (mainboard J1) | 1 | 1 VBUS, 2 D−, 3 D+, 4 GND, 5-6 not connected |
| J3 | USB-A | 2 | USBLC6 (U4) |
| J4 | USB-A | 3 | USBLC6 (U5) |
| J5 | USB-C | 4 | USBLC6 (U6); 56k Rp on CC1/CC2 (default USB power, 500 mA) |

## Hub

- **CH334F** (U1, QFN-24): USB 2.0, high-speed upstream and downstream, one transaction translator per port
  (MTT), so the keyboard's full-speed traffic doesn't hold up a high-speed mouse (an 8 kHz mouse runs at high
  speed and passes straight through). All three back ports and the keyboard share the one 480 Mbit/s link to the PC.
- Bus-powered: PSELF tied low. RESET#/CDP left open (internal pull-up, as the datasheet recommends).
  OVCUR#, PWREN# and the LED pins are not used.
- 12 MHz crystal (Y1) with no load capacitors: the CH334 has them built in (datasheet 1.1).
- V5 from VBUS (10 µF + 100 nF), VDD33 from its own LDO (1 µF + 100 nF).

## Port power

The three back ports share an SY6280AAC current-limited switch (U3, always on, ISET 6.8k) with 3 × 22 µF on
its output; the keyboard port takes VBUS before the switch, so a short on a back port can't reset the keyboard.
Upstream VBUS has 10 µF at most on it (USB's inrush limit).

Everything is powered from the PC's one port: about 500 mA from a USB-A port on the PC, 1.5-3 A from a USB-C port
that offers it. The keyboard's RGB comes out of the same budget (see the mainboard README).

## Open checks

- **SY6280AAC:** the pin order in `Dachshund70-Hub.kicad_sym` (1 OUT, 2 GND, 3 ISET, 4 EN, 5 IN) and the current
  limit (6.8k, expected to give about 1 A) are from memory; check both against Silergy's datasheet before ordering.
- **USB-A footprint:** the XKB U231-091N-4BLRA00-S (C2880618) is a 9-pin (USB 3) receptacle; only pins 1-4 are
  used. Check its front edge against the drawing (placed so its mouth is flush with the board edge).
- USB D+/D− are short 0.15 mm tracks, not impedance-controlled pairs. Keep the board's track lengths short as now;
  if high-speed devices misbehave, make the pairs 90 Ω differential.
- The case needs a new back opening for 2 × USB-A, 2 × USB-C and the board's 80 mm width (case thread).

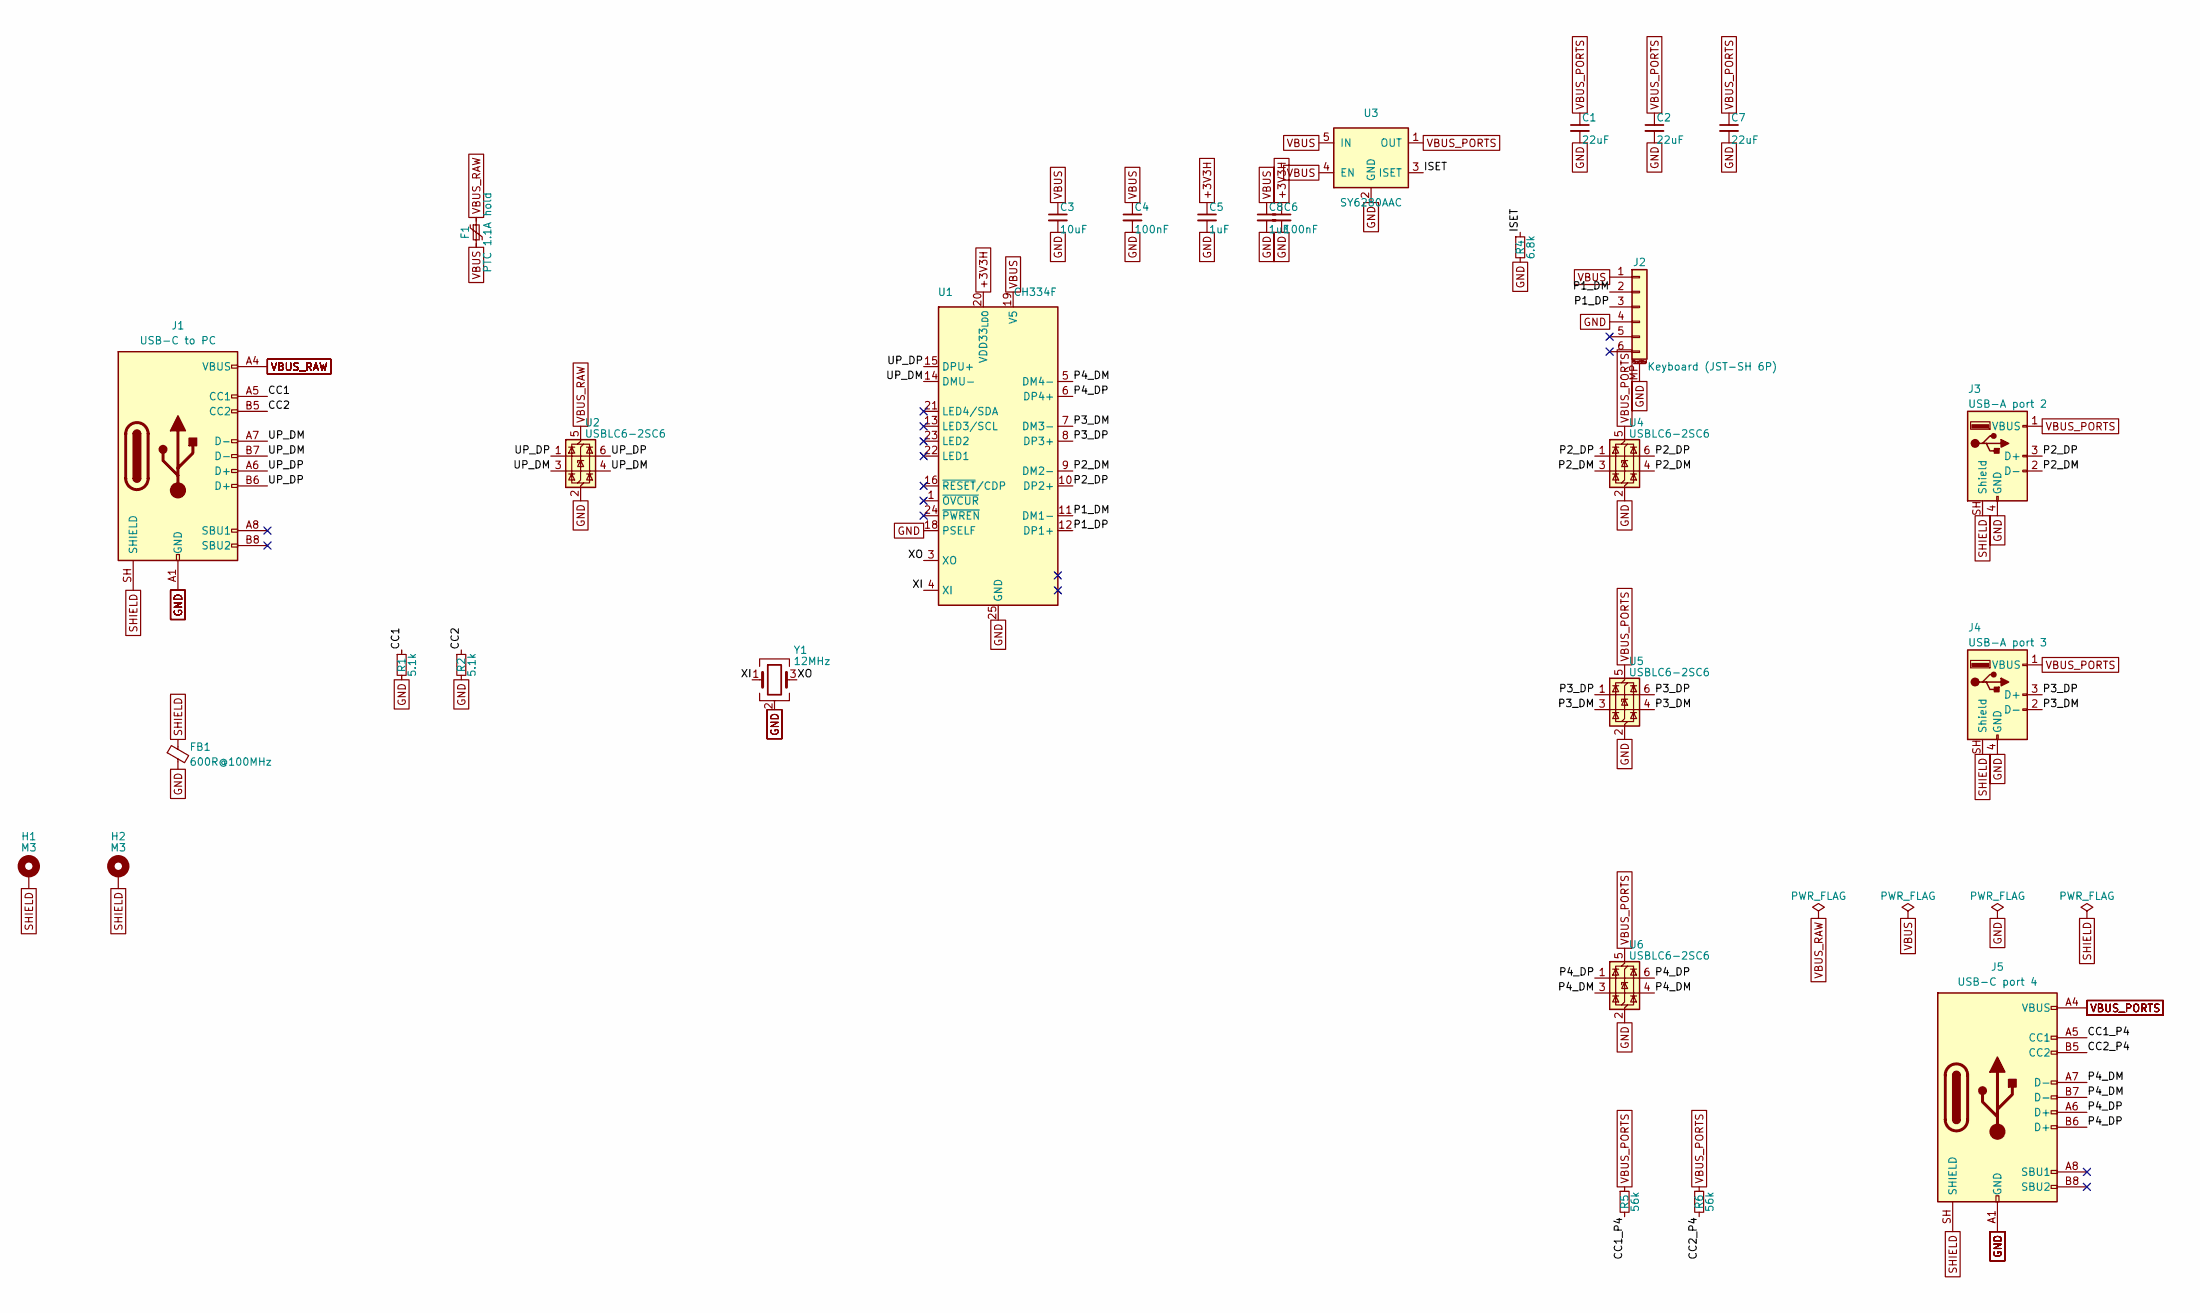
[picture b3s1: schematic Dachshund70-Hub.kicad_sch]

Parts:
C1, C2, C7: 22uF; C_0805_2012Metric; MPN Samsung CL21A226MAQNNNE; LCSC C45783
C3: 10uF; C_0603_1608Metric; MPN Samsung CL10A106KP8NNNC; LCSC C19702
C4, C6: 100nF; C_0402_1005Metric; MPN Samsung CL05B104KO5NNNC; LCSC C1525
C5, C8: 1uF; C_0402_1005Metric; MPN Samsung CL05A105KA5NQNC; LCSC C52923
F1: PTC 1.1A hold; Fuse_1206_3216Metric; MPN SMD1206B110TFT; LCSC C269119
FB1: 600R@100MHz; L_0805_2012Metric; LCSC C1017
H1, H2: M3; MountingHole_3.2mm_M3_ISO7380_Pad_TopBottom
J1: USB-C to PC; USB_C_Receptacle_HRO_TYPE-C-31-M-12; MPN HRO TYPE-C-31-M-12; LCSC C165948
J2: Keyboard (JST-SH 6P); JST_SH_SM06B-SRSS-TB_1x06-1MP_P1.00mm_Horizontal; MPN JST SM06B-SRSS-TB(LF)(SN); LCSC C160405
J3: USB-A port 2; USB_A_Receptacle_XKB_U231-091N-4BLRA00-S; MPN XKB U231-091N-4BLRA00-S; LCSC C2880618
J4: USB-A port 3; USB_A_Receptacle_XKB_U231-091N-4BLRA00-S; MPN XKB U231-091N-4BLRA00-S; LCSC C2880618
J5: USB-C port 4; USB_C_Receptacle_HRO_TYPE-C-31-M-12; MPN HRO TYPE-C-31-M-12; LCSC C165948
R1, R2: 5.1k; R_0402_1005Metric; MPN UNI-ROYAL 0402WGF5101TCE; LCSC C25905
R4: 6.8k; R_0402_1005Metric; MPN UNI-ROYAL 0402WGF6801TCE; LCSC C25917
R5, R6: 56k; R_0402_1005Metric; MPN UNI-ROYAL 0402WGF5602TCE; LCSC C25796
U1: CH334F; QFN-24-1EP_4x4mm_P0.5mm_EP2.7x2.7mm; MPN WCH CH334F; LCSC C5187527
U2, U4, U5, U6: USBLC6-2SC6; SOT-23-6; MPN ST USBLC6-2SC6; LCSC C7519
U3: SY6280AAC; SOT-23-5; MPN Silergy SY6280AAC; LCSC C55136
Y1: 12MHz; Crystal_SMD_3225-4Pin_3.2x2.5mm; MPN YXC X322512MSB4SI; LCSC C9002

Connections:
+3V3H: C5.1, C6.1, U1.20 (VDD33_{LDO})
/CC1: J1.A5 (CC1), R1.1
/CC1_P4: J5.A5 (CC1), R5.2
/CC2: J1.B5 (CC2), R2.1
/CC2_P4: J5.B5 (CC2), R6.2
/ISET: R4.1, U3.3 (ISET)
/P1_DM: J2.2, U1.11 (DM1-)
/P1_DP: J2.3, U1.12 (DP1+)
/P2_DM: J3.2 (D-), U1.9 (DM2-), U4.3 (I/O2), U4.4 (I/O2)
/P2_DP: J3.3 (D+), U1.10 (DP2+), U4.1 (I/O1), U4.6 (I/O1)
/P3_DM: J4.2 (D-), U1.7 (DM3-), U5.3 (I/O2), U5.4 (I/O2)
/P3_DP: J4.3 (D+), U1.8 (DP3+), U5.1 (I/O1), U5.6 (I/O1)
/P4_DM: J5.A7 (D-), J5.B7 (D-), U1.5 (DM4-), U6.3 (I/O2), U6.4 (I/O2)
/P4_DP: J5.A6 (D+), J5.B6 (D+), U1.6 (DP4+), U6.1 (I/O1), U6.6 (I/O1)
/UP_DM: J1.A7 (D-), J1.B7 (D-), U1.14 (DMU-), U2.3 (I/O2), U2.4 (I/O2)
/UP_DP: J1.A6 (D+), J1.B6 (D+), U1.15 (DPU+), U2.1 (I/O1), U2.6 (I/O1)
/XI: U1.4 (XI), Y1.1
/XO: U1.3 (XO), Y1.3
GND: C1.2, C2.2, C3.2, C4.2, C5.2, C6.2, C7.2, C8.2, FB1.2, J1.A1 (GND), J1.A12 (GND), J1.B1 (GND), J1.B12 (GND), J2.4, J2.MP (MountPin), J3.4 (GND), J4.4 (GND), J5.A1 (GND), J5.A12 (GND), J5.B1 (GND), J5.B12 (GND), R1.2, R2.2, R4.2, U1.18 (PSELF), U1.25 (GND), U2.2 (GND), U3.2 (GND), U4.2 (GND), U5.2 (GND), U6.2 (GND), Y1.2 (G), Y1.4 (G)
SHIELD: FB1.1, H1.1, H2.1, J1.SH (SHIELD), J3.SH (Shield), J4.SH (Shield), J5.SH (SHIELD)
VBUS: C3.1, C4.1, C8.1, F1.2, J2.1, U1.19 (V5), U3.4 (EN), U3.5 (IN)
VBUS_PORTS: C1.1, C2.1, C7.1, J3.1 (VBUS), J4.1 (VBUS), J5.A4 (VBUS), J5.A9 (VBUS), J5.B4 (VBUS), J5.B9 (VBUS), R5.1, R6.1, U3.1 (OUT), U4.5 (VBUS), U5.5 (VBUS), U6.5 (VBUS)
VBUS_RAW: F1.1, J1.A4 (VBUS), J1.A9 (VBUS), J1.B4 (VBUS), J1.B9 (VBUS), U2.5 (VBUS)

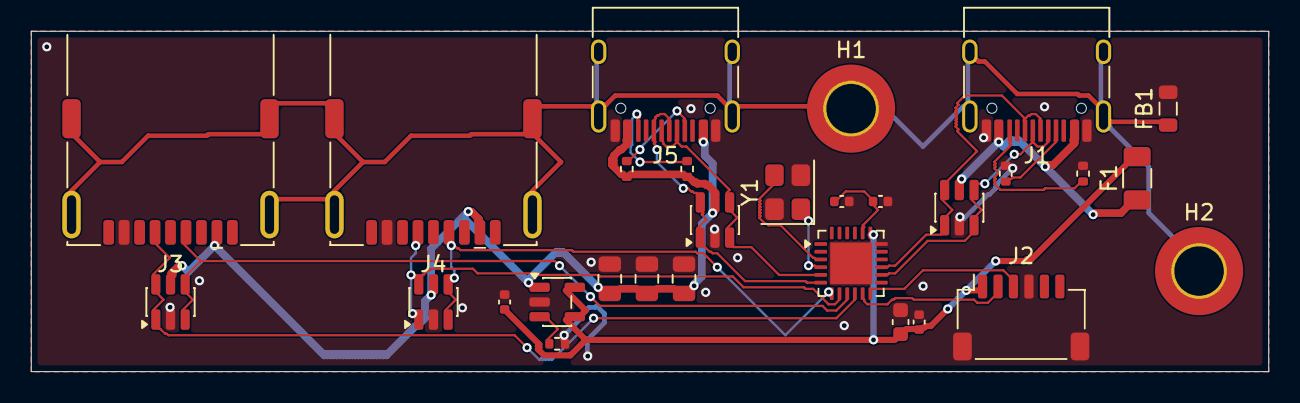
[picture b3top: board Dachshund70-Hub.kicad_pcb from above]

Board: 2 copper layers, 80.0 x 22.0 mm, 29 parts (0 on the bottom side), 23 nets.
